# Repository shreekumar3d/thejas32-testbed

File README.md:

# Status

We're at v1.0, and the board is being tested out.

Do look at the respective directories for hardware and software.

#  Intro

CDAC sells the [ARIES series of boards](https://vegaprocessors.in/devboards/) based on the [THEJAS32 microcontroller](https://vegaprocessors.in/soc/).
The boards can be programmed using the Arduino IDE. Unfortunately, the schematics
of these are not made available.  Documentation about the THEJAS32 SoC itself
is scarce as well, though the chip itself is available for [purchase on robu.in
in single quantity](https://robu.in/product/thejas32-soc-based-microprocessor/).

This project (and follow on work) will try to fill this gap, as I find more.
This is a board design for a learner board based on the THEJAS32
microcontroller. It is the first open source board based on 
the THEJAS32. This is part of a much larger effort to document THEJAS32 
and its ecosystem and make it usuable.

THEJAS32 runs directly on an external clock, offering a single core 100
MHz RISC-V CPU with a IO interfaces - UART, SPI, I2C, PWM and GPIOs.

This board sets up THEJAS32 a test microcontroller, controlled by a Raspberry
Pi Pico.  Some of the IO interfaces are routed to the Pico.  This opens
the door for many types of experimentation and learning, including clock
control, timing, peripheral emulation, etc.  

Useful background and goals for this board are well covered in my [recent talk
at IndiaFOSS 2024](https://youtu.be/-m1KqcOkT5M?t=6345) (video, 25 mins). There
is also a [AtiVEGA hackaday project](https://hackaday.io/project/197724-ativega) page.
Look at hackaday for updates, what's going on in the project, etc.

A somewhat detailed background and intro to the
board is also in [this presentation at ChennaiFOSS 2024 conference](https://www.youtube.com/watch?v=wljsP2YMgHc)
(video, 25 minutes) that I gave earlier this year.

This board is designed to be a low cost board, relying on off-the-shelf components
as much as possible.  The goal is to encourage easy assembly without advanced
skills. For this reason, the smallest footprint chosen for passives is 0603.

# Design

The board consists of a few main elements

* THEJAS32 SoC
* 2 MB flash (used by THEJAS32)
* Raspberry Pi Pico
* 2x Mini 360 DC-DC power modules - one to generate core voltage of 1.2V, other for 3.3V

The core of the board consists of

* THEJAS32 SoC
* 2 MB flash

The power and boot cycle of the THEJAS32 ("MCU") is primarily controlled 
using a few pins

* active low RESET can be pulled up by Master Pico to get it out of reset
* System clock is generated from a GPOUT capable pin of the Pico. System 
  clock can thus be generated in many ways
* BOOT_SEL pin is controlled by Pico, allowing boot from SPI flash
  or UART.
* BOOT UART (UART0) is routed to Pico, enabling log capture and 
  programming

Pins and interfaces are broken out into standard 0.1" headers. Dual
row headers are mostly employed. When shorted, the interface gets routed from
the MCU to the RP2040. This enables advanced experimentation, precise timing,
peripheral emulation, co-processing, etc.

Board may be powered using the dedicated micro USB connector(J2) or through
the Pico.  Jumpers JP3 and JP4 decide the source of power. Both jumpers may
also be populated, allowing the Pico to function as a USB host, but care must
be taken not to connect Pico as a USB device in such cases. Refer to the schematic
for more info.

Precise measurement of power draw of the THEJAS32 is also a goal of this board. Jumpers JP2 and JP1 are included for this purpose.

# THEJAS32 IO

All IOs from THEJAS32 are broken out. Software can thus use all the pins. Some details are below; do refer the schematics for complete details.

## UART

Boot UART is available on J3. This can be sent to the Pico for control, by using two jumpers.

J11 breaks out UART1 from THEJAS32.

## Raspberry Pi HAT compatibility

Many Raspberry Pi HATs should be usable with this board, mounted on J12.
THEJAS32 does not have any pin multiplexing. The most commonly used 
functions on the various pins are thus directly assigned, including I2C,
SPI, UART and PWM and GPIOs. Refer the schematics for details.

A full size HAT can be mounted on this board. Additional through holes are 
provided to ensure mechanical support.

## GPIO Breakout

J10 features 14 GPIOs - GPIO17 to GPIO30. States for these can be set one shot, by bit masking.

## I2C and SPI

J4 breaks out I2C1 and SPI0.

J13 provides access to I2C0.  This is also connected to the Pico, for control. Pico can be setup as an I2C slave and respond to I2C transfers initiated by THEJAS32.

Similarly SPI1 is available on J9, also connected to SPI interface on Pico. Pico can be setup as a SPI slave, and respong to transfers initiated by THEJAS32.

## JTAG

J5 breaks out JTAG pins from THEJAS32.  Fun fact: none of the official ARIES boards break out JTAG.

## PWM

PWM pins 4,5,6 are broken out on J7. R32, R33 and R34 can be used to control the current.

# Raspberry Pi Pico

Pico controls the runtime lifecycle of the THEJAS32, via the RESET and CLK pins. BOOT_SEL is also under Pico's control. Note that the Pico is an integral part of the board design, as it provides the clock signal to THEJAS32.

J8 and J6 can be used to interface external electronics directly to Pico. J8 has the debug UART.

A single ADC pin, clock pin (GPIO22) are available as well.

# Tools

Based on KiCAD 8.

# Checkout Instructions

This project uses git submodules. To checkout everything, do:

    git clone --recurse-submodules https://github.com/shreekumar3d/thejas32-testbed.git

Raspberry Pi Pico footprint is a submodule.  If you don't go this, you'll not
see the nice Pico in the 3D preview.

# Credits

* [RPi Pico Symbool and Footprint](https://github.com/ncarandini/KiCad-RP-Pico)
* [Mini 360 Step Down Converter Footprint](https://github.com/rayvburn/KiCad)

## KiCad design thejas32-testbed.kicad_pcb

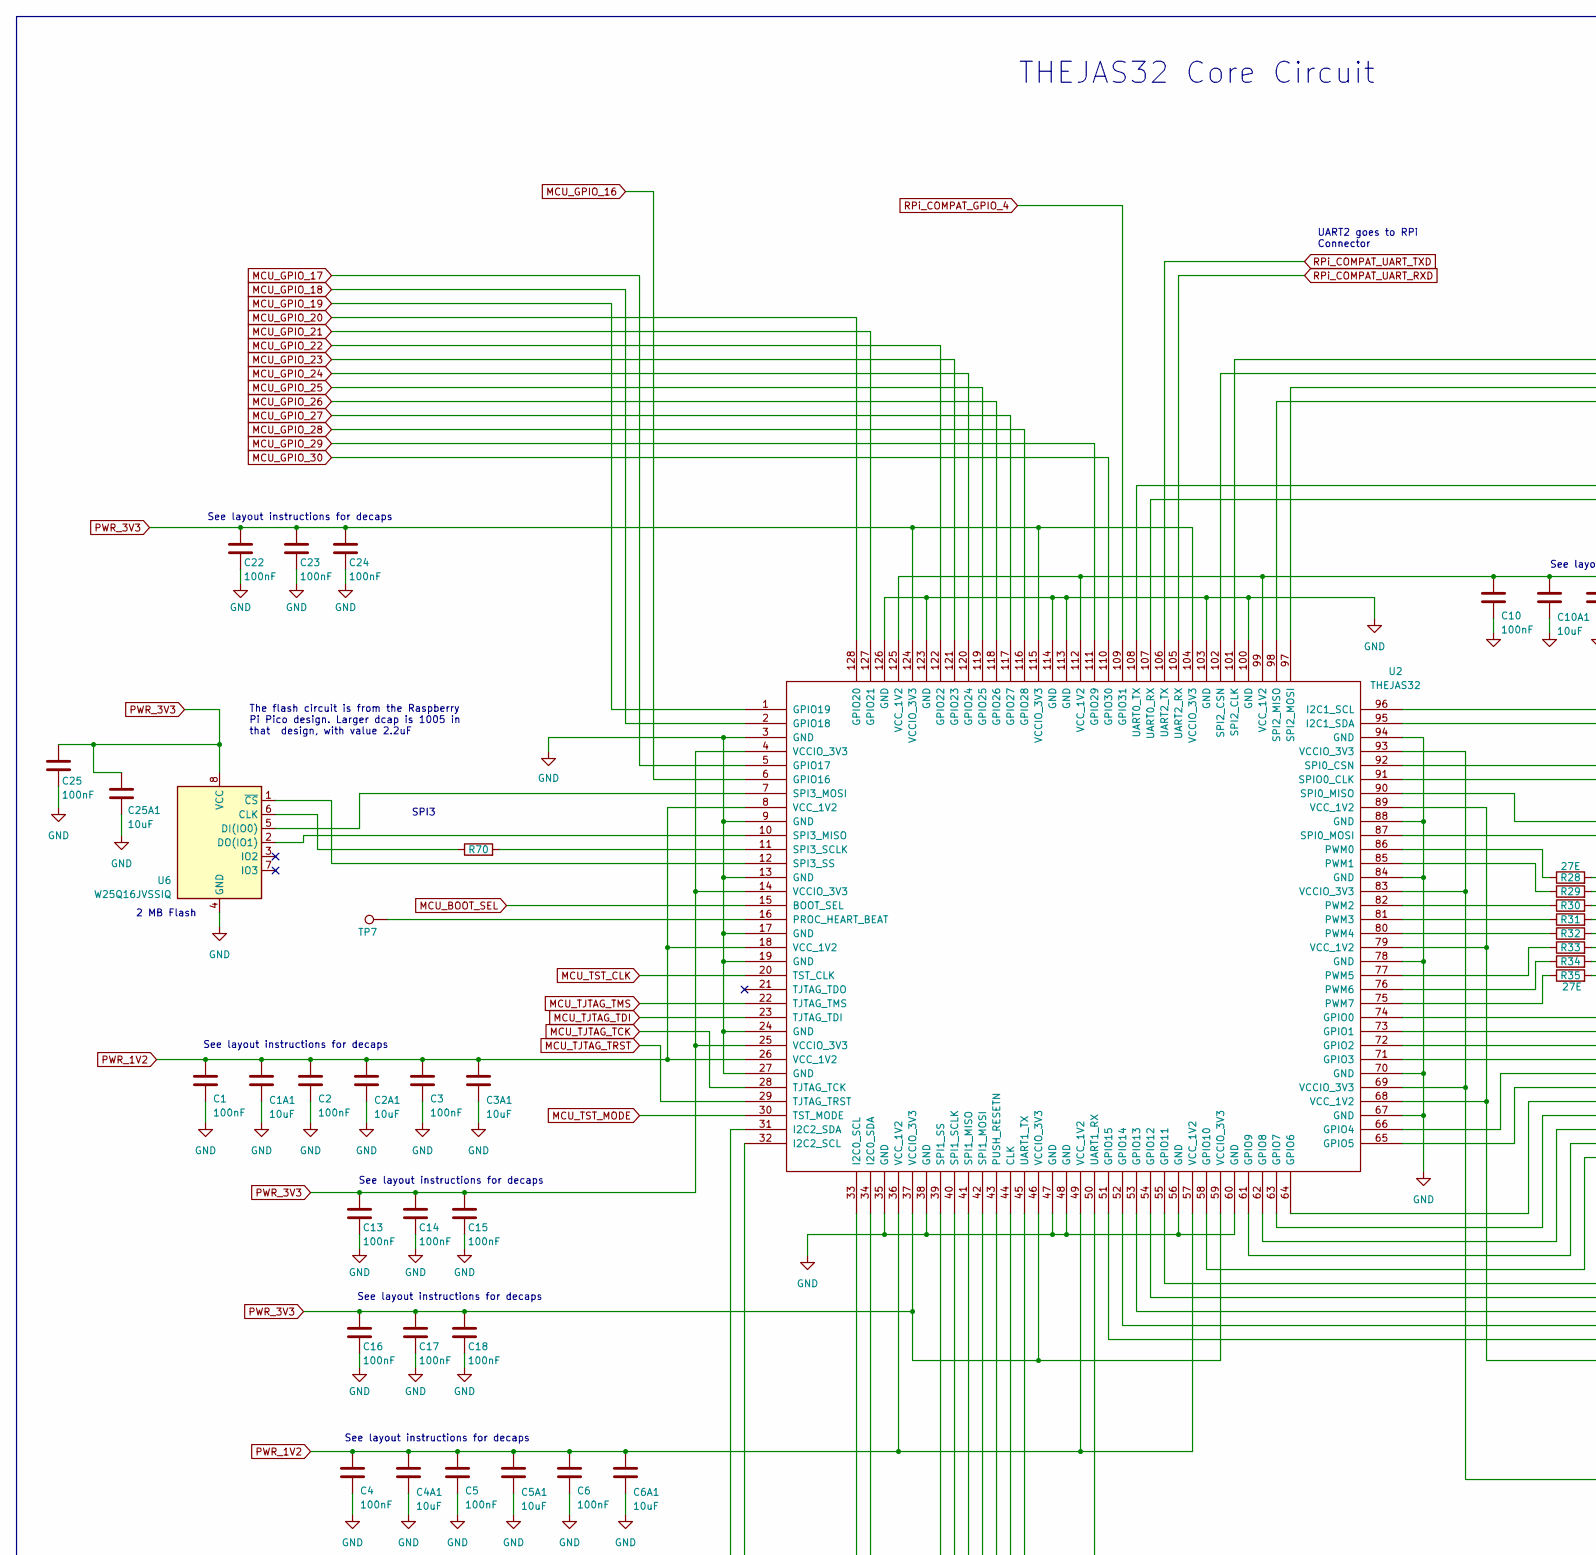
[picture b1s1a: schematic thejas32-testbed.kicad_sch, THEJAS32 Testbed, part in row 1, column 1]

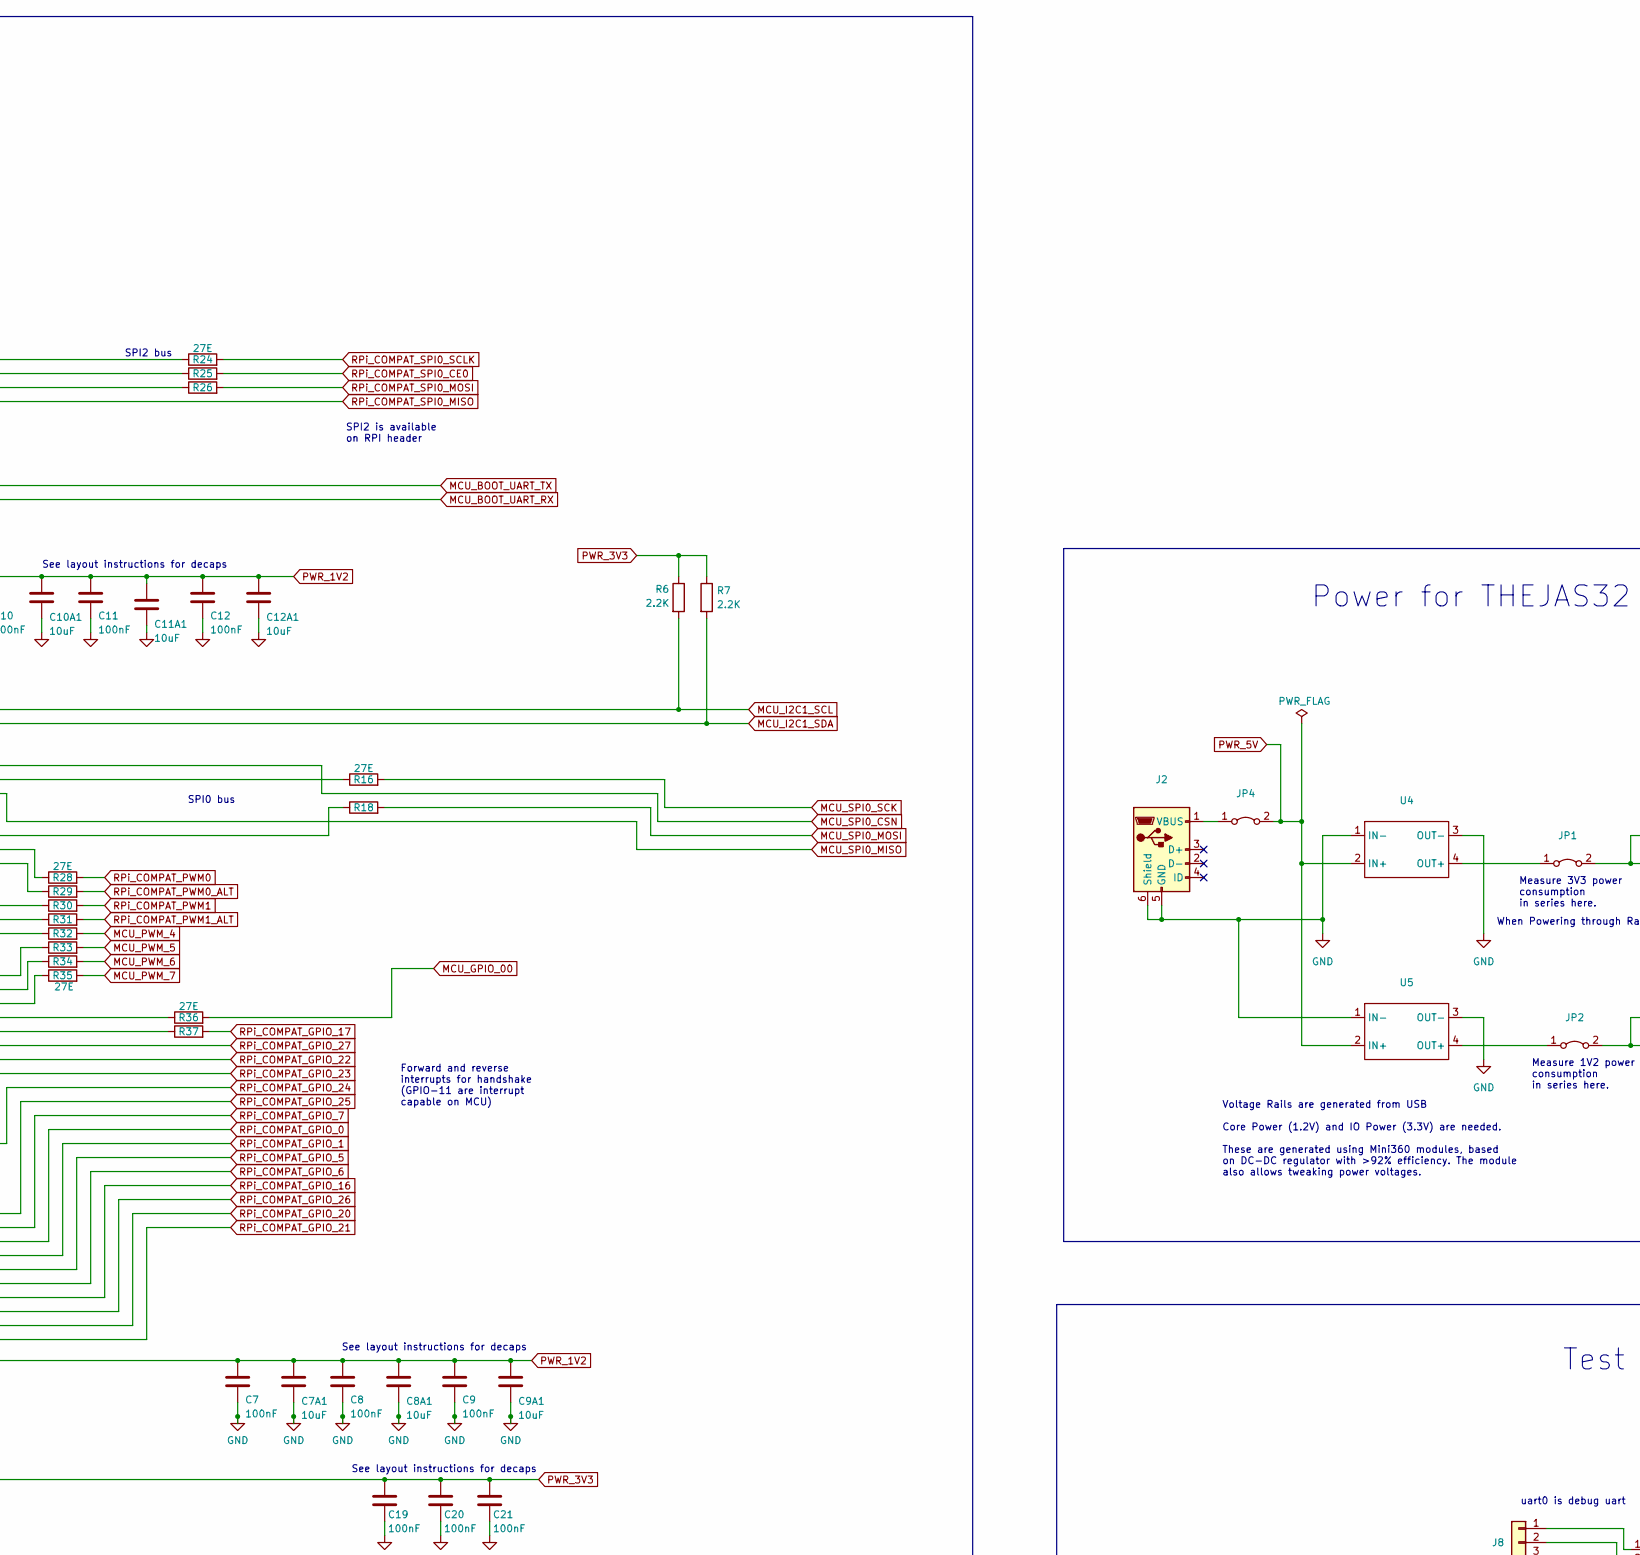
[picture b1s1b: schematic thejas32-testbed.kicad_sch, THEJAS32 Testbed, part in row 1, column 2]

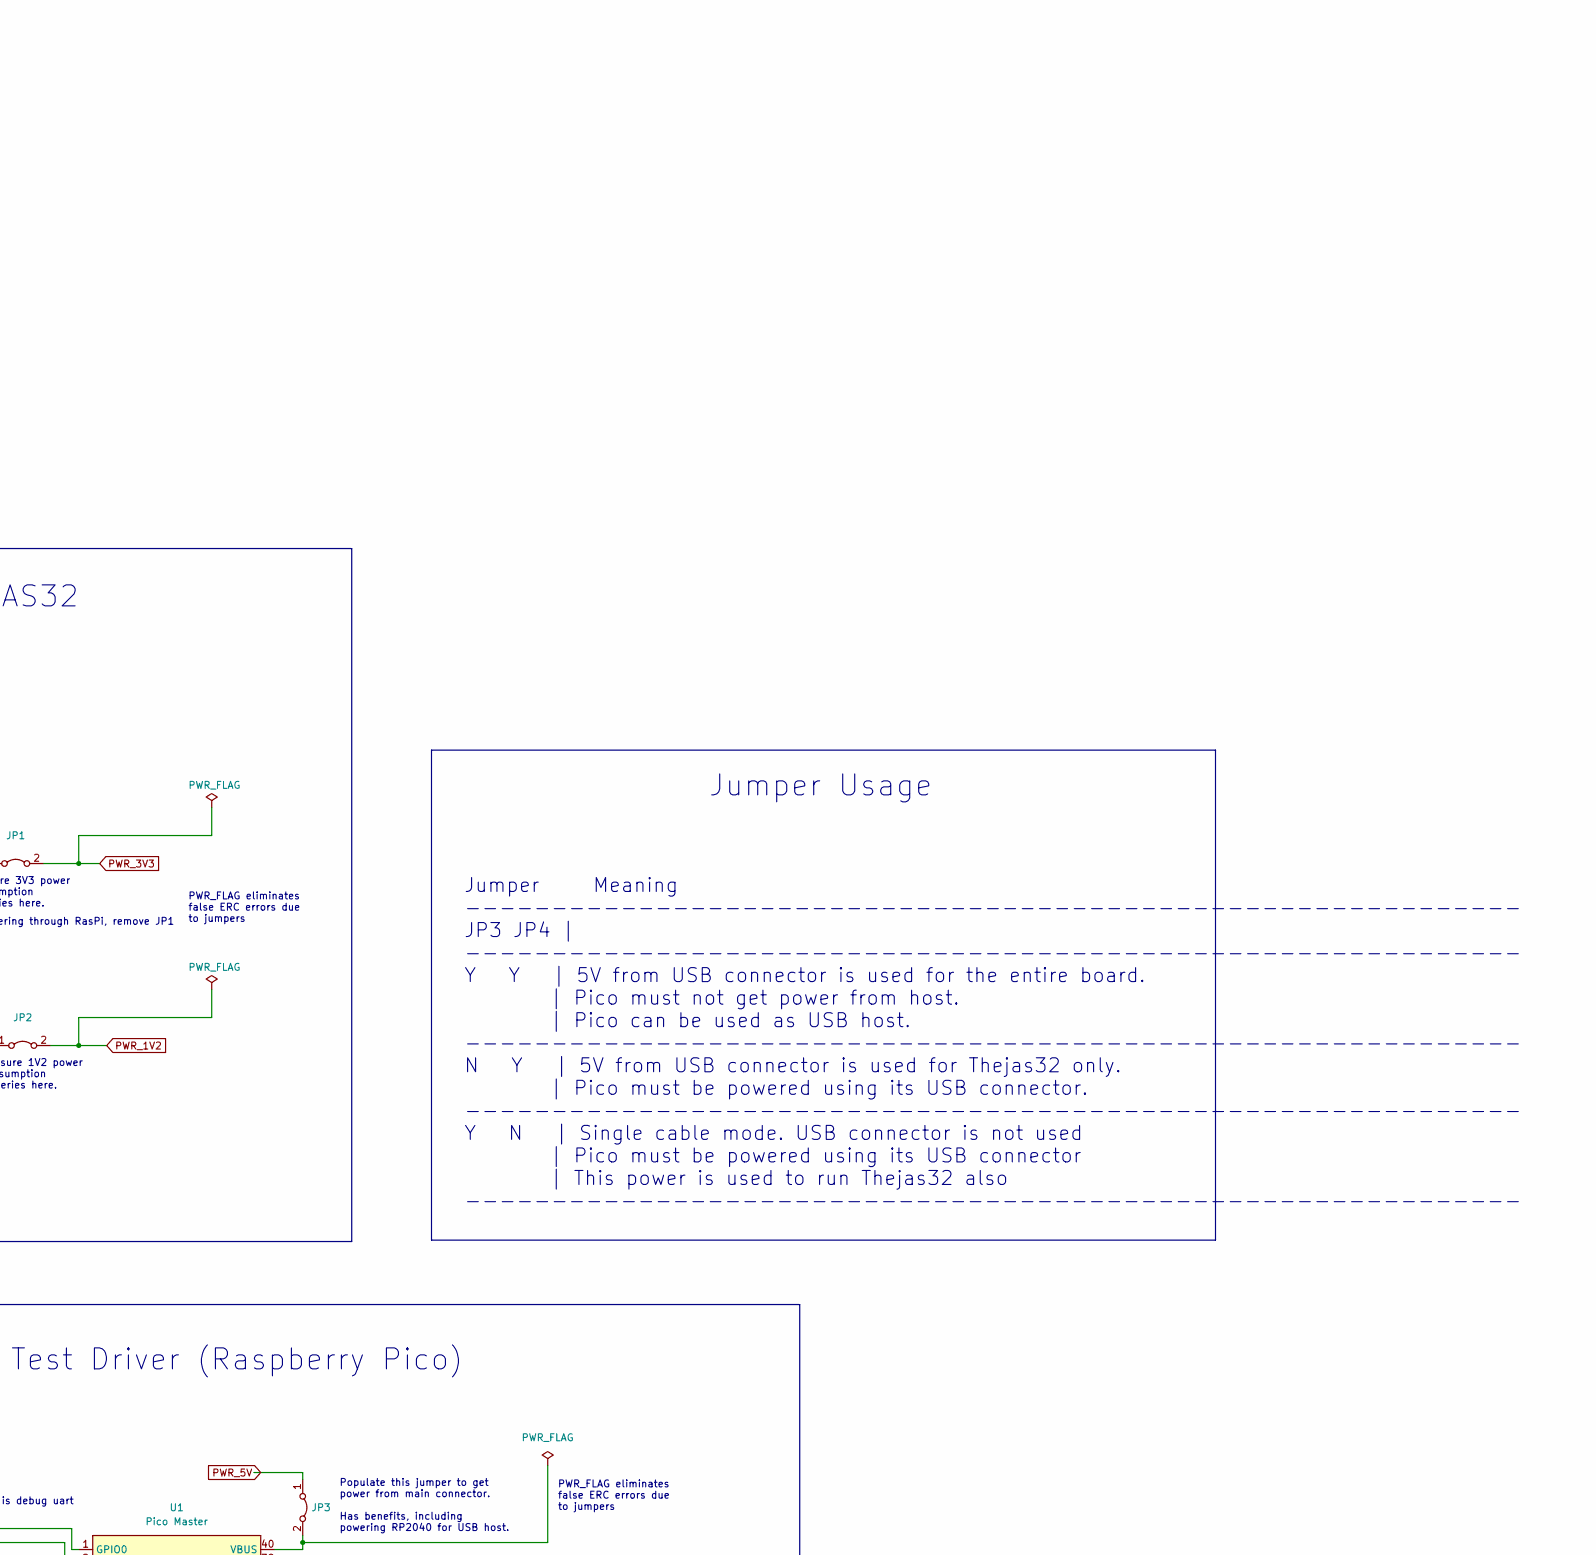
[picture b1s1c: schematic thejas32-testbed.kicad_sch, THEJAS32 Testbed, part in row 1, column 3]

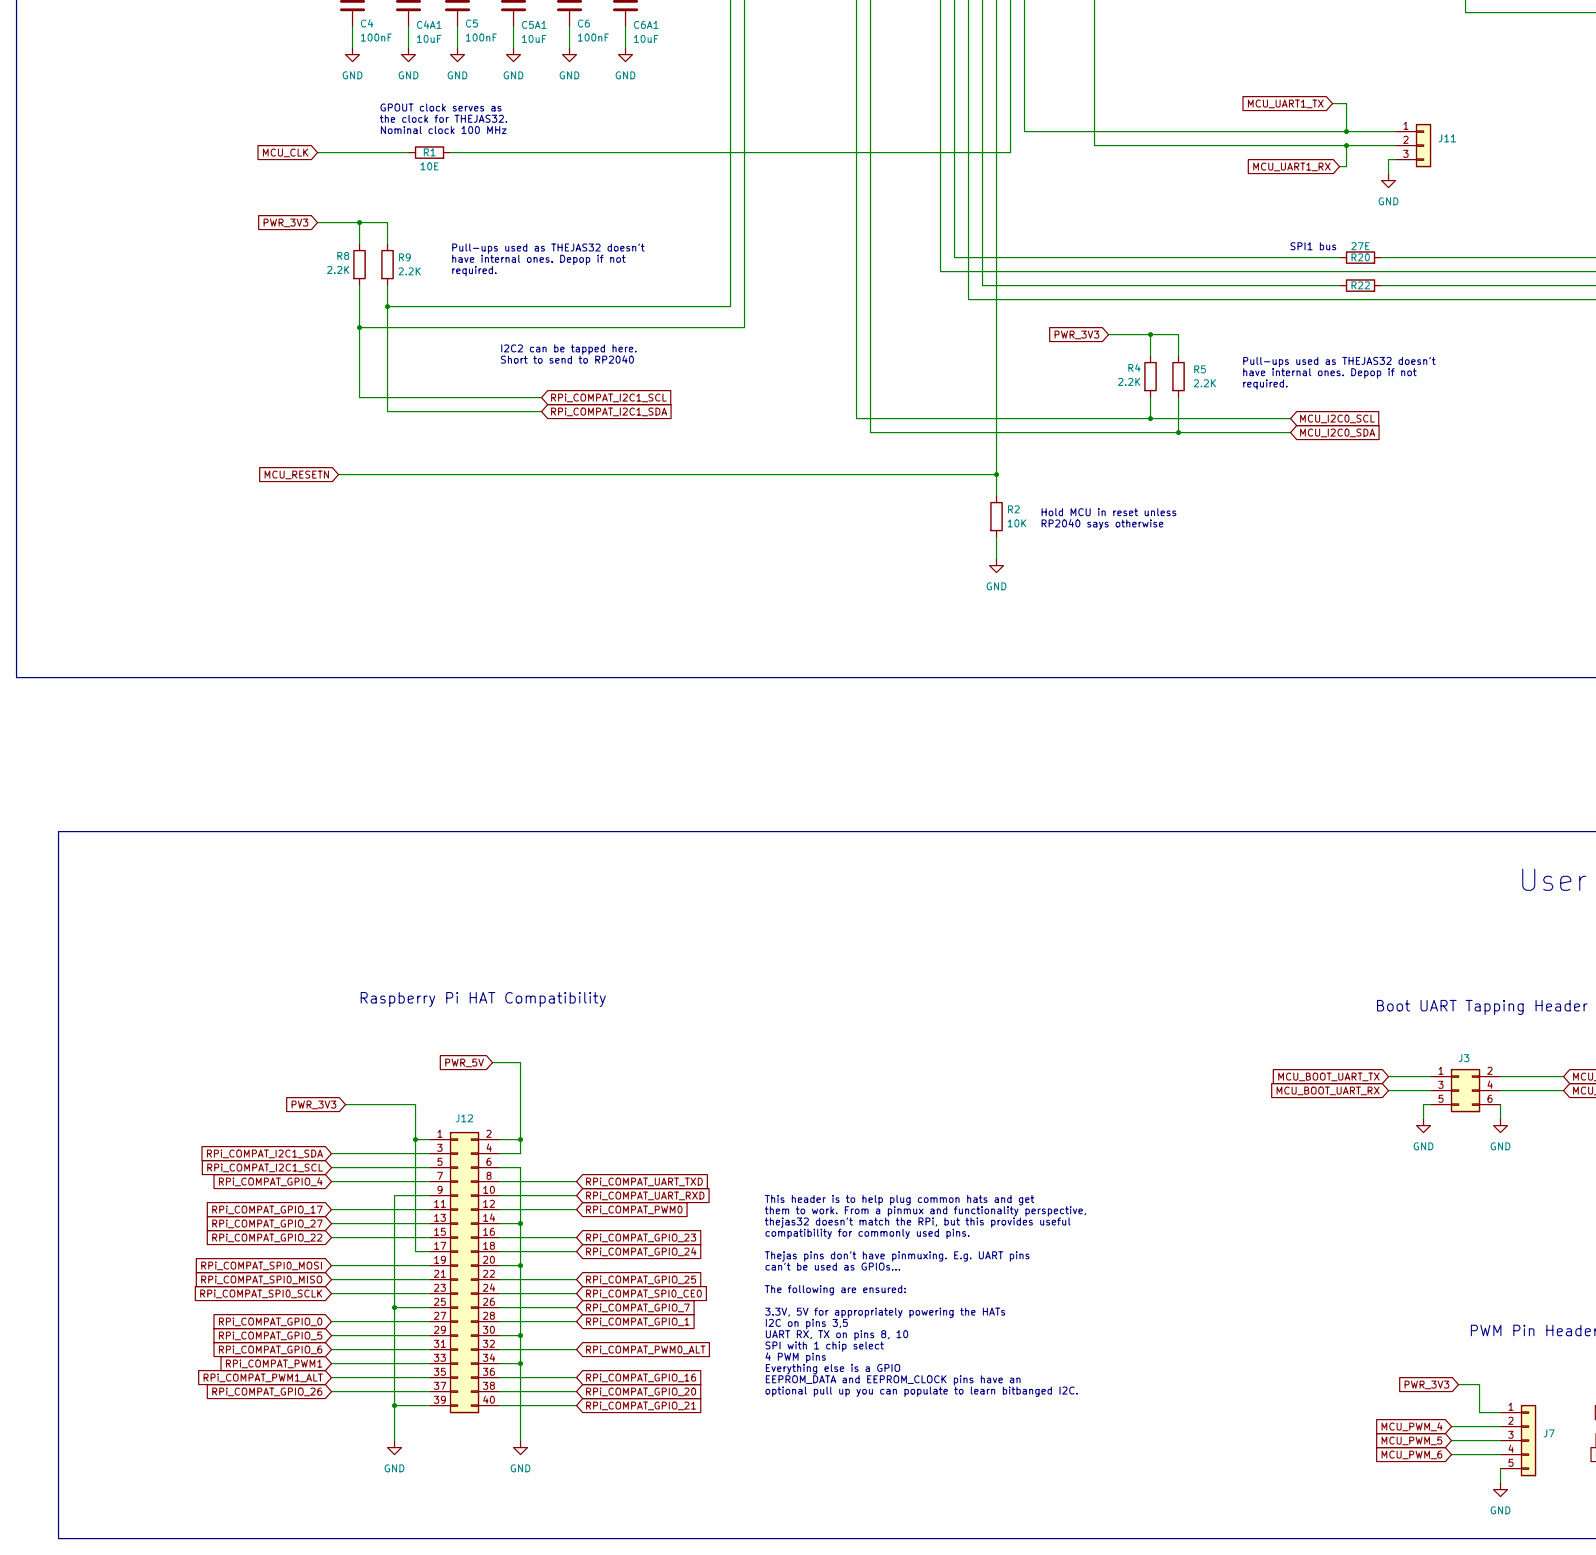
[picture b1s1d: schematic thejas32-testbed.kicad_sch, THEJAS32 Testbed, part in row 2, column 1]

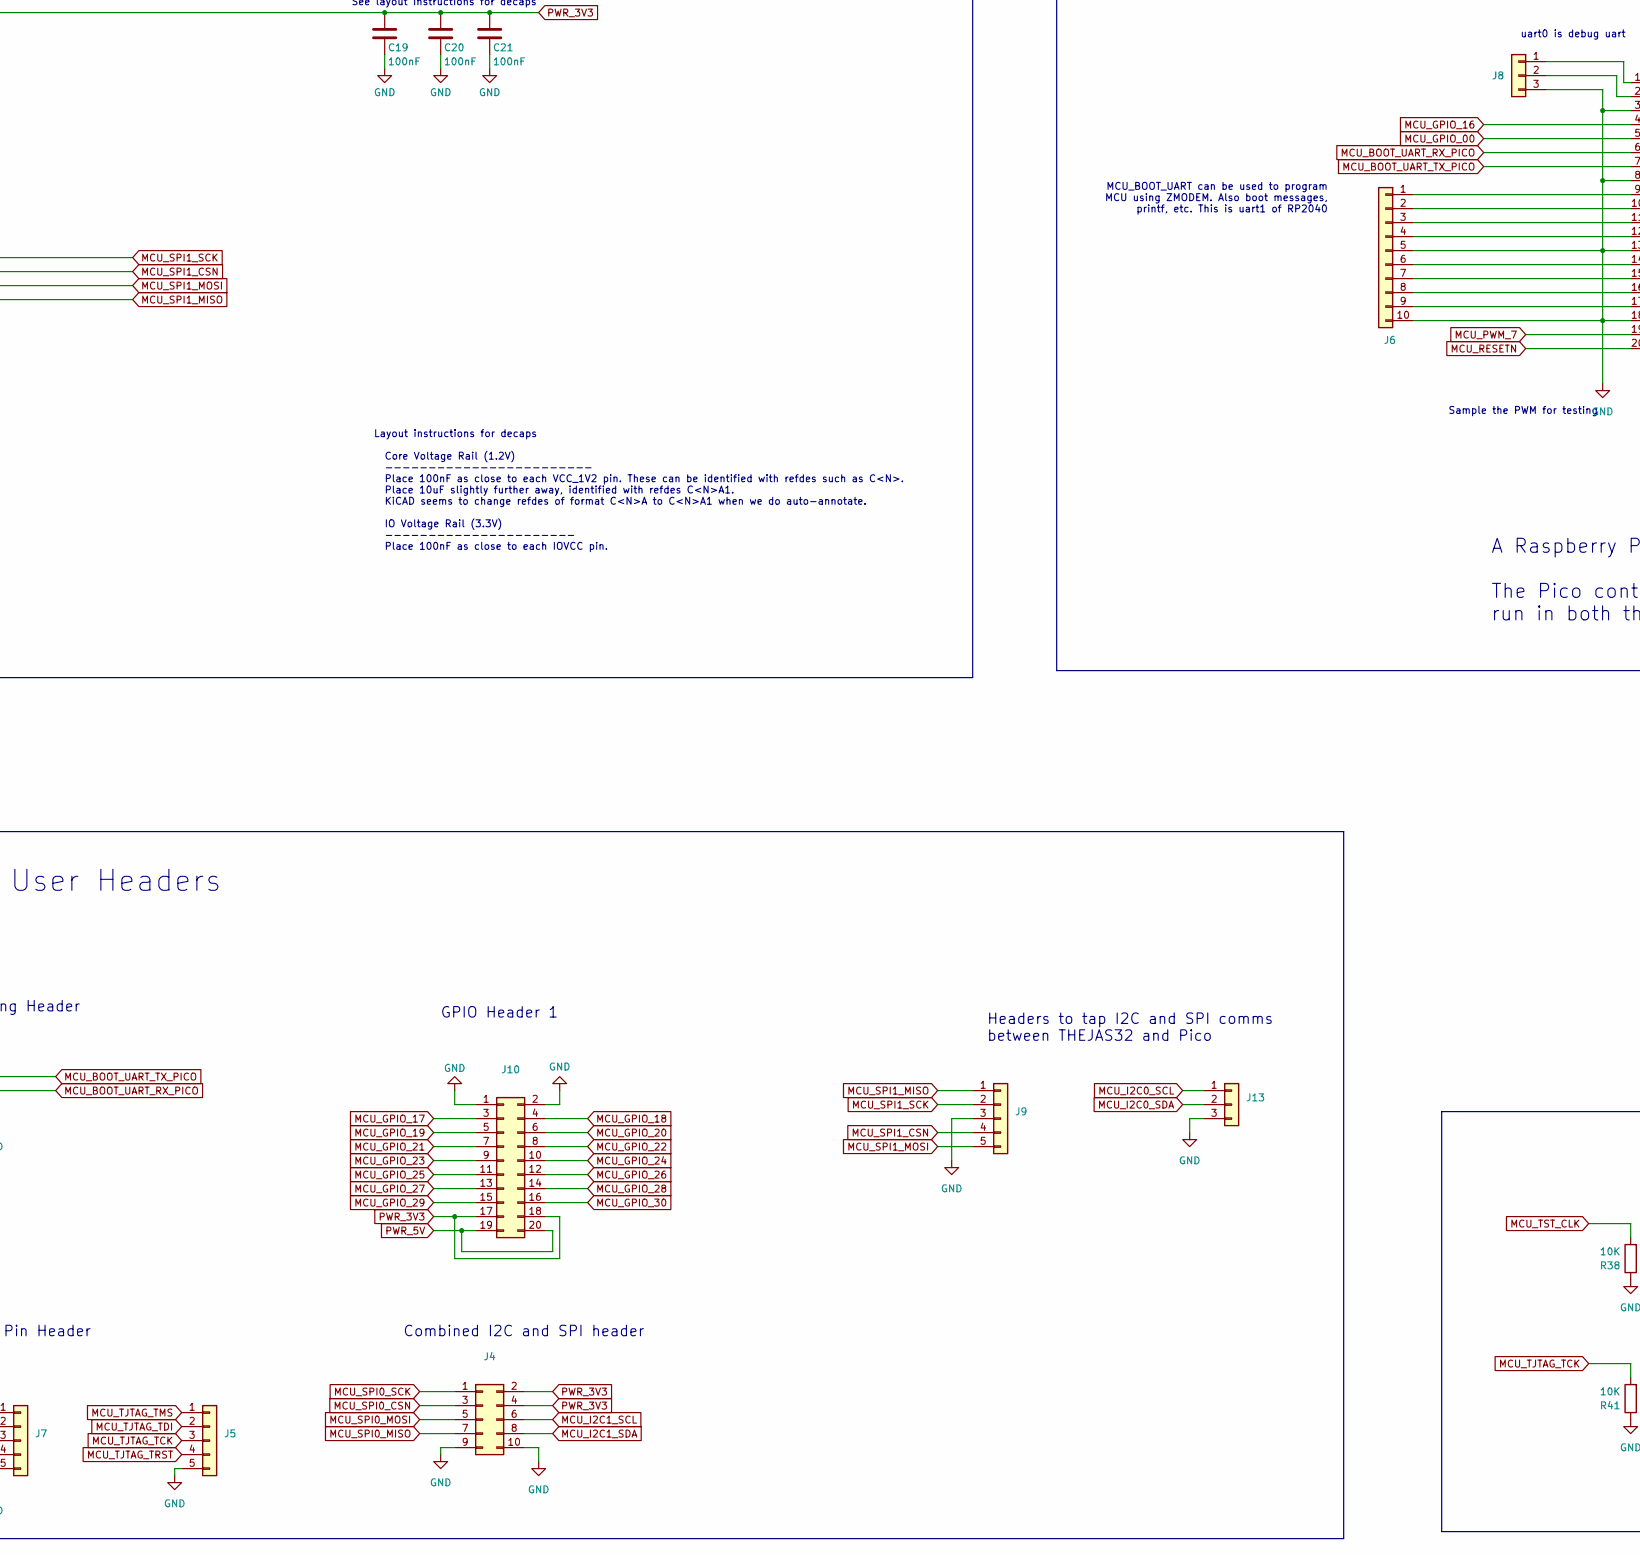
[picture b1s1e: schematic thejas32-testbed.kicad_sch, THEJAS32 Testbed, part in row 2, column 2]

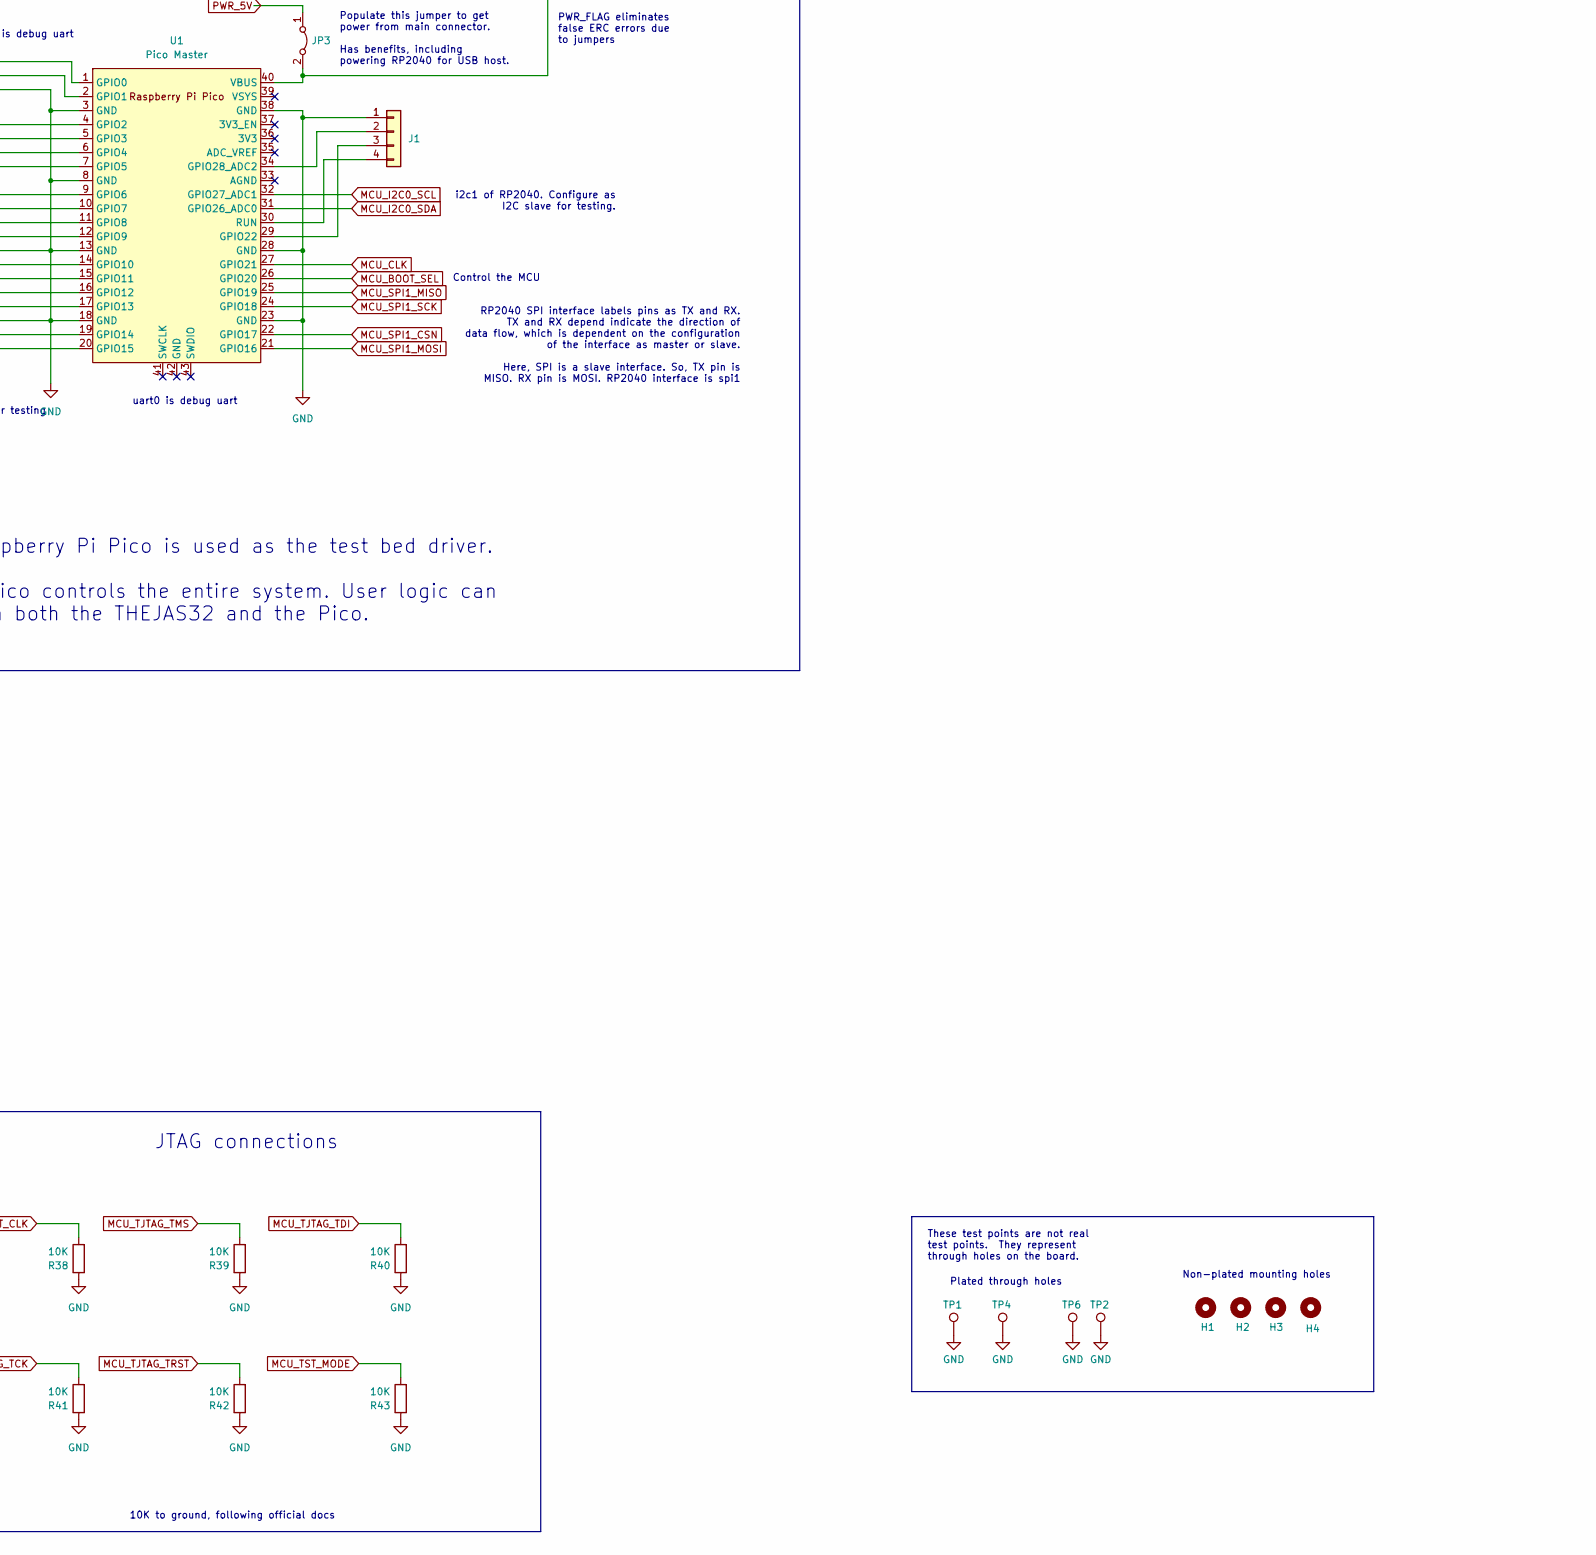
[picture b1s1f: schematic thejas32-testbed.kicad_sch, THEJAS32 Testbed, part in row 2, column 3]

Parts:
C1, C2, C3, C4, C5, C6, C7, C8, C9, C10, C11, C12, C13, C14, C15, C16, C17, C18, C19, C20, C21, C22, C23, C24, C25: 100nF; proj_C_0603_1608Metric_Pad1.08x0.95mm_HandSolder; MPN 5190
C1A1, C2A1, C3A1, C4A1, C5A1, C6A1, C7A1, C8A1, C9A1, C10A1, C11A1, C12A1, C25A1: 10uF; proj_C_0603_1608Metric_Pad1.08x0.95mm_HandSolder; MPN 6799
H1, H2, H3, H4: MountingHole; MountingHole_3mm
J1: Conn_01x04; PinHeader_1x04_P2.54mm_Vertical; MPN 2.54 mm 1x4 pin male header
J2: USB_B_Micro; USB_Micro-B_Molex-105017-0001; MPN 4653
J3: Conn_02x03_Odd_Even; PinHeader_2x03_P2.54mm_Vertical; MPN 2.54 mm 2x3 pin male header
J4: Conn_02x05_Odd_Even; PinHeader_2x05_P2.54mm_Vertical; MPN 2.54 mm 2x5 pin male header
J5, J7, J9: Conn_01x05; PinHeader_1x05_P2.54mm_Vertical; MPN 2.54 mm 1x5 pin male header
J6: Conn_01x10; PinHeader_1x10_P2.54mm_Vertical; MPN 2.54 mm 1x10 pin male header
J8, J11, J13: Conn_01x03; PinHeader_1x03_P2.54mm_Vertical; MPN 2.54 mm 1x3 pin male header
J10: Conn_02x10_Odd_Even; PinHeader_2x10_P2.54mm_Vertical; MPN 2.54 mm 2x10 pin male header
J12: Conn_02x20_Odd_Even; PinHeader_2x20_P2.54mm_Vertical; MPN 2.54 mm 2x20 pin male header
JP1, JP2, JP3, JP4: Jumper_2_Bridged; PinHeader_1x02_P2.54mm_Vertical; MPN 2.54 mm 1x2 pin male header
R1, R70: 10E; proj_R_0603_1608Metric_Pad0.98x0.95mm_HandSolder; MPN 5354
R2, R38, R39, R40, R41, R42, R43: 10K; proj_R_0603_1608Metric_Pad0.98x0.95mm_HandSolder; MPN 5192
R4, R5, R6, R7, R8, R9: 2.2K; proj_R_0603_1608Metric_Pad0.98x0.95mm_HandSolder; MPN 6735
R16, R18, R20, R22, R24, R25, R26, R28, R29, R30, R31, R32, R33, R34, R35, R36, R37: 27E; proj_R_0603_1608Metric_Pad0.98x0.95mm_HandSolder; MPN 5297
TP1, TP2, TP4, TP6: Mounting Hole; MountingHole_3.2mm_M3_Pad_TopBottom
TP7: TestPoint; TestPoint_Pad_1.0x1.0mm
U1: Pico Master; RPi_Pico_SMD_TH; MPN Raspberry Pi Pico
U2: THEJAS32; LQFP-128_14x14mm_P0.4mm; MPN THEJAS32
U4, U5: Mini360_step-down; MPN 790469
U6: W25Q16JVSSIQ; SOIC-8_5.23x5.23mm_P1.27mm; MPN W25Q16JVSSIQ

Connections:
GND: C1.2, C1A1.2, C2.2, C2A1.2, C3.2, C3A1.2, C4.2, C4A1.2, C5.2, C5A1.2, C6.2, C6A1.2, C7.2, C7A1.2, C8.2, C8A1.2, C9.2, C9A1.2, C10.2, C10A1.2, C11.2, C11A1.2, C12.2, C12A1.2, C13.2, C14.2, C15.2, C16.2, C17.2, C18.2, C19.2, C20.2, C21.2, C22.2, C23.2, C24.2, C25.2, C25A1.2, J1.1, J2.5 (GND), J2.6 (Shield), J3.5, J3.6, J4.9, J4.10, J5.5, J6.5, J6.10, J7.5, J8.3, J9.3, J10.1, J10.2, J11.3, J12.6, J12.9, J12.14, J12.20, J12.25, J12.30, J12.34, J12.39, J13.3, R2.2, R38.1, R39.1, R40.1, R41.1, R42.1, R43.1, TP1.1, TP2.1, TP4.1, TP6.1, U1.3 (GND), U1.8 (GND), U1.13 (GND), U1.18 (GND), U1.23 (GND), U1.28 (GND), U1.38 (GND), U2.3 (GND), U2.9 (GND), U2.13 (GND), U2.17 (GND), U2.19 (GND), U2.24 (GND), U2.27 (GND), U2.35 (GND), U2.38 (GND), U2.47 (GND), U2.48 (GND), U2.56 (GND), U2.60 (GND), U2.67 (GND), U2.70 (GND), U2.78 (GND), U2.84 (GND), U2.88 (GND), U2.94 (GND), U2.100 (GND), U2.103 (GND), U2.113 (GND), U2.114 (GND), U2.123 (GND), U2.126 (GND), U4.1 (IN-), U4.3 (OUT-), U5.1 (IN-), U5.3 (OUT-), U6.4 (GND)
MCU_BOOT_SEL: U1.26 (GPIO20), U2.15 (BOOT_SEL)
MCU_BOOT_UART_RX: J3.3, U2.107 (UART0_RX)
MCU_BOOT_UART_RX_PICO: J3.4, U1.6 (GPIO4)
MCU_BOOT_UART_TX: J3.1, U2.108 (UART0_TX)
MCU_BOOT_UART_TX_PICO: J3.2, U1.7 (GPIO5)
MCU_CLK: R1.1, U1.27 (GPIO21)
MCU_GPIO_00: R36.2, U1.5 (GPIO3)
MCU_GPIO_16: U1.4 (GPIO2), U2.6 (GPIO16)
MCU_GPIO_17: J10.3, U2.5 (GPIO17)
MCU_GPIO_18: J10.4, U2.2 (GPIO18)
MCU_GPIO_19: J10.5, U2.1 (GPIO19)
MCU_GPIO_20: J10.6, U2.128 (GPIO20)
MCU_GPIO_21: J10.7, U2.127 (GPIO21)
MCU_GPIO_22: J10.8, U2.122 (GPIO22)
MCU_GPIO_23: J10.9, U2.121 (GPIO23)
MCU_GPIO_24: J10.10, U2.120 (GPIO24)
MCU_GPIO_25: J10.11, U2.119 (GPIO25)
MCU_GPIO_26: J10.12, U2.118 (GPIO26)
MCU_GPIO_27: J10.13, U2.117 (GPIO27)
MCU_GPIO_28: J10.14, U2.116 (GPIO28)
MCU_GPIO_29: J10.15, U2.111 (GPIO29)
MCU_GPIO_30: J10.16, U2.110 (GPIO30)
MCU_I2C0_SCL: J13.1, R4.2, U1.32 (GPIO27_ADC1), U2.33 (I2C0_SCL)
MCU_I2C0_SDA: J13.2, R5.2, U1.31 (GPIO26_ADC0), U2.34 (I2C0_SDA)
MCU_I2C1_SCL: J4.6, R6.2, U2.96 (I2C1_SCL)
MCU_I2C1_SDA: J4.8, R7.2, U2.95 (I2C1_SDA)
MCU_PWM_4: J7.2, R32.2
MCU_PWM_5: J7.3, R33.2
MCU_PWM_6: J7.4, R34.2
MCU_PWM_7: R35.2, U1.19 (GPIO14)
MCU_RESETN: R2.1, U1.20 (GPIO15), U2.43 (PUSH_RESETN)
MCU_SPI0_CSN: J4.3, U2.92 (SPI0_CSN)
MCU_SPI0_MISO: J4.7, U2.90 (SPI0_MISO)
MCU_SPI0_MOSI: J4.5, R18.2
MCU_SPI0_SCK: J4.1, R16.2
MCU_SPI1_CSN: J9.4, U1.22 (GPIO17), U2.39 (SPI1_SS)
MCU_SPI1_MISO: J9.1, U1.25 (GPIO19), U2.41 (SPI1_MISO)
MCU_SPI1_MOSI: J9.5, R22.2, U1.21 (GPIO16)
MCU_SPI1_SCK: J9.2, R20.2, U1.24 (GPIO18)
MCU_TJTAG_TCK: J5.3, R41.2, U2.28 (TJTAG_TCK)
MCU_TJTAG_TDI: J5.2, R40.2, U2.23 (TJTAG_TDI)
MCU_TJTAG_TMS: J5.1, R39.2, U2.22 (TJTAG_TMS)
MCU_TJTAG_TRST: J5.4, R42.2, U2.29 (TJTAG_TRST)
MCU_TST_CLK: R38.2, U2.20 (TST_CLK)
MCU_TST_MODE: R43.2, U2.30 (TST_MODE)
MCU_UART1_RX: J11.2, U2.50 (UART1_RX)
MCU_UART1_TX: J11.1, U2.45 (UART1_TX)
unnamed: J1.2, U1.34 (GPIO28_ADC2)
unnamed: J1.3, U1.29 (GPIO22)
unnamed: J1.4, U1.30 (RUN)
unnamed: J2.1 (VBUS), JP4.1 (A)
unnamed: J6.1, U1.9 (GPIO6)
unnamed: J6.2, U1.10 (GPIO7)
unnamed: J6.3, U1.11 (GPIO8)
unnamed: J6.4, U1.12 (GPIO9)
unnamed: J6.6, U1.14 (GPIO10)
unnamed: J6.7, U1.15 (GPIO11)
unnamed: J6.8, U1.16 (GPIO12)
unnamed: J6.9, U1.17 (GPIO13)
unnamed: J8.1, U1.1 (GPIO0)
unnamed: J8.2, U1.2 (GPIO1)
unnamed: JP1.1 (A), U4.4 (OUT+)
unnamed: JP2.1 (A), U5.4 (OUT+)
unnamed: JP3.2 (B), U1.40 (VBUS)
unnamed: R1.2, U2.44 (CLK)
unnamed: R36.1, U2.74 (GPIO0)
unnamed: R37.1, U2.73 (GPIO1)
unnamed: TP7.1, U2.16 (PROC_HEART_BEAT)
unnamed: R28.1, U2.86 (PWM0)
unnamed: R29.1, U2.85 (PWM1)
unnamed: R30.1, U2.82 (PWM2)
unnamed: R31.1, U2.81 (PWM3)
unnamed: R32.1, U2.80 (PWM4)
unnamed: R33.1, U2.77 (PWM5)
unnamed: R34.1, U2.76 (PWM6)
unnamed: R35.1, U2.75 (PWM7)
unnamed: R18.1, U2.87 (SPI0_MOSI)
unnamed: R22.1, U2.42 (SPI1_MOSI)
unnamed: R20.1, U2.40 (SPI1_SCLK)
unnamed: R24.1, U2.101 (SPI2_CLK)
unnamed: R25.1, U2.102 (SPI2_CSN)
unnamed: R26.1, U2.97 (SPI2_MOSI)
unnamed: U2.10 (SPI3_MISO), U6.2 (DO(IO1))
unnamed: U2.7 (SPI3_MOSI), U6.5 (DI(IO0))
unnamed: R70.2, U2.11 (SPI3_SCLK)
unnamed: U2.12 (SPI3_SS), U6.1 (~CS)
unnamed: R16.1, U2.91 (SPIO0_CLK)
unnamed: R70.1, U6.6 (CLK)
PWR_1V2: C1.1, C1A1.1, C2.1, C2A1.1, C3.1, C3A1.1, C4.1, C4A1.1, C5.1, C5A1.1, C6.1, C6A1.1, C7.1, C7A1.1, C8.1, C8A1.1, C9.1, C9A1.1, C10.1, C10A1.1, C11.1, C11A1.1, C12.1, C12A1.1, JP2.2 (B), U2.8 (VCC_1V2), U2.18 (VCC_1V2), U2.26 (VCC_1V2), U2.36 (VCC_1V2), U2.49 (VCC_1V2), U2.57 (VCC_1V2), U2.68 (VCC_1V2), U2.79 (VCC_1V2), U2.89 (VCC_1V2), U2.99 (VCC_1V2), U2.112 (VCC_1V2), U2.125 (VCC_1V2)
PWR_3V3: C13.1, C14.1, C15.1, C16.1, C17.1, C18.1, C19.1, C20.1, C21.1, C22.1, C23.1, C24.1, C25.1, C25A1.1, J4.2, J4.4, J7.1, J10.17, J10.18, J12.1, J12.17, JP1.2 (B), R4.1, R5.1, R6.1, R7.1, R8.1, R9.1, U2.4 (VCCIO_3V3), U2.14 (VCCIO_3V3), U2.25 (VCCIO_3V3), U2.37 (VCCIO_3V3), U2.46 (VCCIO_3V3), U2.59 (VCCIO_3V3), U2.69 (VCCIO_3V3), U2.83 (VCCIO_3V3), U2.93 (VCCIO_3V3), U2.104 (VCCIO_3V3), U2.115 (VCCIO_3V3), U2.124 (VCCIO_3V3), U6.8 (VCC)
PWR_5V: J10.19, J10.20, J12.2, J12.4, JP3.1 (A), JP4.2 (B), U4.2 (IN+), U5.2 (IN+)
RPi_COMPAT_GPIO_0: J12.27, U2.62 (GPIO8)
RPi_COMPAT_GPIO_1: J12.28, U2.61 (GPIO9)
RPi_COMPAT_GPIO_4: J12.7, U2.109 (GPIO31)
RPi_COMPAT_GPIO_5: J12.29, U2.58 (GPIO10)
RPi_COMPAT_GPIO_6: J12.31, U2.55 (GPIO11)
RPi_COMPAT_GPIO_7: J12.26, U2.63 (GPIO7)
RPi_COMPAT_GPIO_16: J12.36, U2.54 (GPIO12)
RPi_COMPAT_GPIO_17: J12.11, R37.2
RPi_COMPAT_GPIO_20: J12.38, U2.52 (GPIO14)
RPi_COMPAT_GPIO_21: J12.40, U2.51 (GPIO15)
RPi_COMPAT_GPIO_22: J12.15, U2.71 (GPIO3)
RPi_COMPAT_GPIO_23: J12.16, U2.66 (GPIO4)
RPi_COMPAT_GPIO_24: J12.18, U2.65 (GPIO5)
RPi_COMPAT_GPIO_25: J12.22, U2.64 (GPIO6)
RPi_COMPAT_GPIO_26: J12.37, U2.53 (GPIO13)
RPi_COMPAT_GPIO_27: J12.13, U2.72 (GPIO2)
RPi_COMPAT_I2C1_SCL: J12.5, R8.2, U2.32 (I2C2_SCL)
RPi_COMPAT_I2C1_SDA: J12.3, R9.2, U2.31 (I2C2_SDA)
RPi_COMPAT_PWM0: J12.12, R28.2
RPi_COMPAT_PWM0_ALT: J12.32, R29.2
RPi_COMPAT_PWM1: J12.33, R30.2
RPi_COMPAT_PWM1_ALT: J12.35, R31.2
RPi_COMPAT_SPI0_CE0: J12.24, R25.2
RPi_COMPAT_SPI0_MISO: J12.21, U2.98 (SPI2_MISO)
RPi_COMPAT_SPI0_MOSI: J12.19, R26.2
RPi_COMPAT_SPI0_SCLK: J12.23, R24.2
RPi_COMPAT_UART_RXD: J12.10, U2.105 (UART2_RX)
RPi_COMPAT_UART_TXD: J12.8, U2.106 (UART2_TX)

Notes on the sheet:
These test points are not real test points. They represent through holes on the board.
MCU_BOOT_UART can be used to program MCU using ZMODEM. Also boot messages, printf, etc. This is uart1 of RP2040
i2c1 of RP2040. Configure as I2C slave for testing.
uart0 is debug uart
See layout instructions for decaps
Raspberry Pi HAT Compatibility
Boot UART Tapping Header
THEJAS32 Core Circuit
UART2 goes to RPi Connector
Combined I2C and SPI header
Sample the PWM for testing
Forward and reverse interrupts for handshake (GPIO-11 are interrupt capable on MCU)
10K to ground, following official docs
Headers to tap I2C and SPI comms between THEJAS32 and Pico
When Powering through RasPi, remove JP1
SPI2 bus
I2C2 can be tapped here. Short to send to RP2040
This header is to help plug common hats and get them to work. From a pinmux and functionality perspective, thejas32 doesn't match the RPi, but this provides useful compatibility for commonly used pins. Thejas pins don't have pinmuxing. E.g. UART pins can't be used as GPIOs... The following are ensu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
Layout instructions for decaps Core Voltage Rail (1.2V) ------------------------ Place 100nF as close to each VCC_1V2 pin. These can be identified with refdes such as C<N>. Place 10uF slightly further away, identified with refdes C<N>A1. KiCAD seems to change refdes of format C<N>A to C<N>A1 when w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
Power for THEJAS32
Pull-ups used as THEJAS32 doesn't have internal ones. Depop if not required.
RP2040 SPI interface labels pins as TX and RX. TX and RX depend indicate the direction of data flow, which is dependent on the configuration of the interface as master or slave. Here, SPI is a slave interface. So, TX pin is MISO. RX pin is MOSI. RP2040 interface is spi1
JTAG connections
Hold MCU in reset unless RP2040 says otherwise
Populate this jumper to get power from main connector. Has benefits, including powering RP2040 for USB host.
Non-plated mounting holes
SPI1 bus
The flash circuit is from the Raspberry Pi Pico design. Larger dcap is 1005 in that design, with value 2.2uF
Measure 1V2 power consumption in series here.
PWM Pin Header
Voltage Rails are generated from USB Core Power (1.2V) and IO Power (3.3V) are needed. These are generated using Mini360 modules, based on DC-DC regulator with >92% efficiency. The module also allows tweaking power voltages.
Plated through holes
GPOUT clock serves as the clock for THEJAS32. Nominal clock 100 MHz
Jumper Meaning ------------------------------------------------------------- JP3 JP4 | ------------------------------------------------------------- Y Y | 5V from USB connector is used for the entire board. | Pico must not get power from host. | Pico can be used as USB host. -----------------------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
Test Driver (Raspberry Pico)
PWR_FLAG eliminates false ERC errors due to jumpers
SPI2 is available on RPI header
User Headers
GPIO Header 1
Jumper Usage
